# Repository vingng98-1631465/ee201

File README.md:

# EE 201
## This is a practice file for fundamentals.
### Changed this for the sake of the practice.

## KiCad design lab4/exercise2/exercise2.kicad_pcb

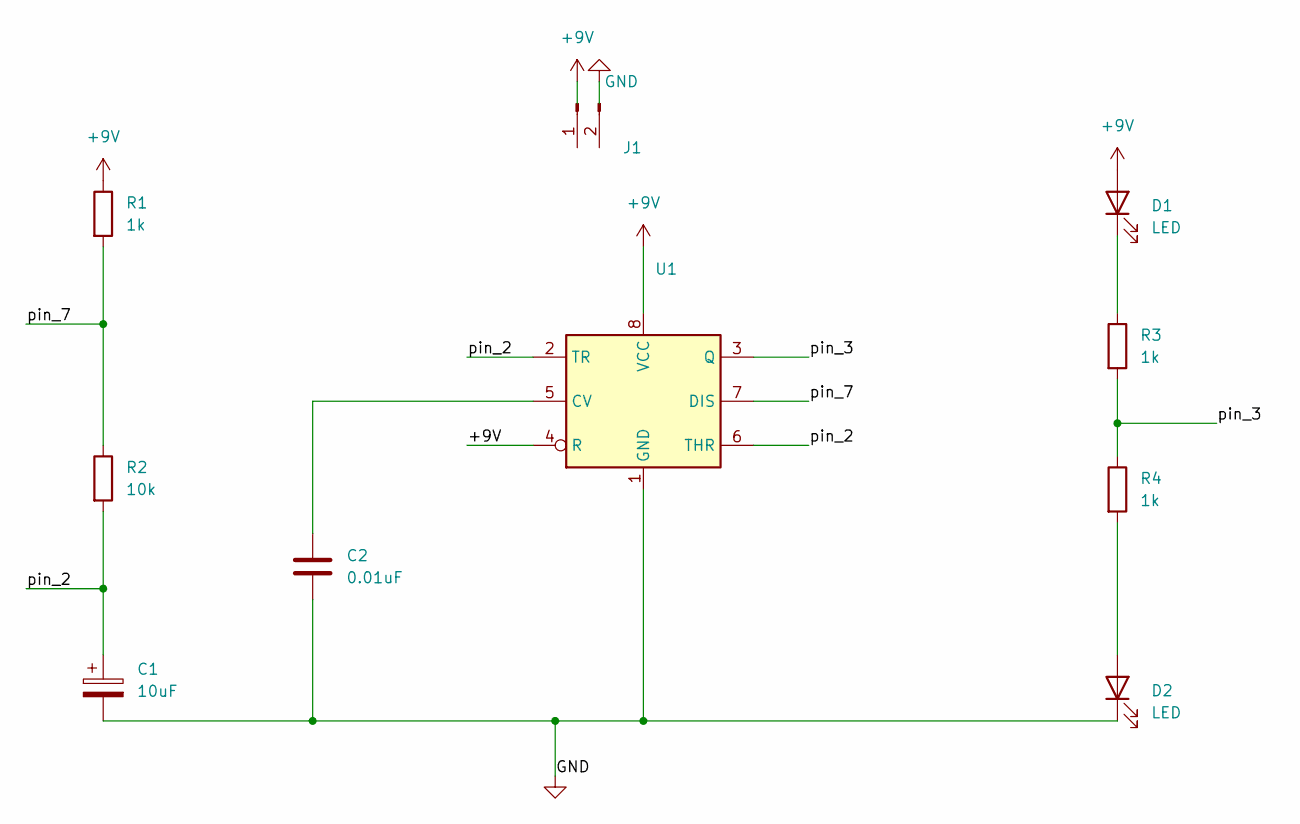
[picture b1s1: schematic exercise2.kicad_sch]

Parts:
C1: 10uF; CP_EIA-3216-18_Kemet-A_Pad1.58x1.35mm_HandSolder
C2: 0.01uF; C_0805_2012Metric_Pad1.18x1.45mm_HandSolder
D1, D2: LED; LED_1206_3216Metric_Pad1.42x1.75mm_HandSolder
J1: J1; TerminalBlock_bornier-2_P5.08mm
R1, R3, R4: 1k; R_0805_2012Metric_Pad1.20x1.40mm_HandSolder
R2: 10k; R_0805_2012Metric_Pad1.20x1.40mm_HandSolder
U1: U1; SOIC-8-1EP_3.9x4.9mm_P1.27mm_EP2.29x3mm

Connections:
+9V: D1.2 (A), R1.1, U1.4 (R), U1.8 (VCC)
/pin_2: C1.1, R2.2, U1.2 (TR), U1.6 (THR)
/pin_3: R3.2, R4.1, U1.3 (Q)
/pin_7: R1.2, R2.1, U1.7 (DIS)
GND: C1.2, C2.2, D2.1 (K), U1.1 (GND)
unnamed: C2.1, U1.5 (CV)
unnamed: D1.1 (K), R3.1
unnamed: D2.2 (A), R4.2

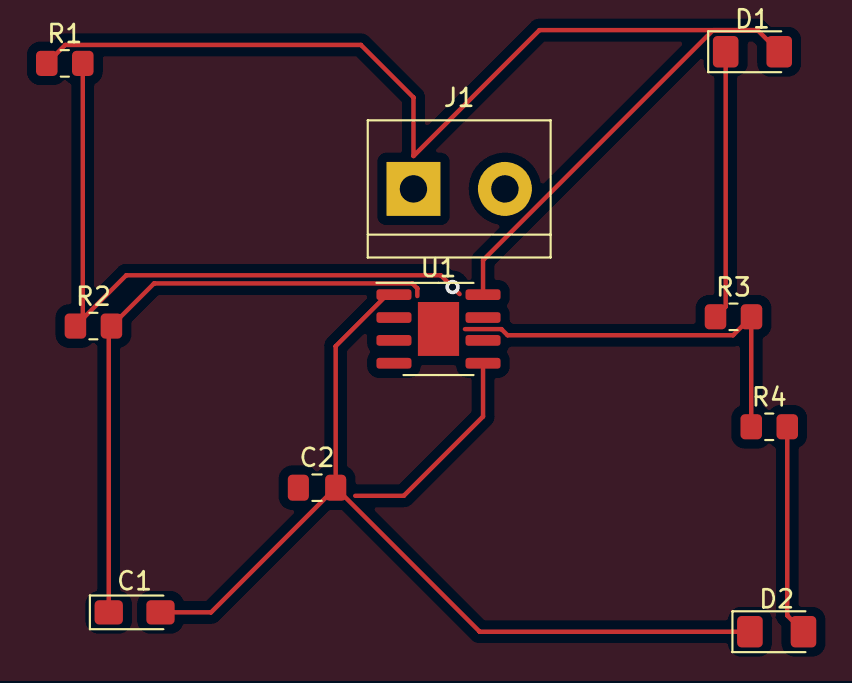
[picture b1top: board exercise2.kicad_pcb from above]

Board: 2 copper layers, 10 parts (0 on the bottom side), 8 nets.

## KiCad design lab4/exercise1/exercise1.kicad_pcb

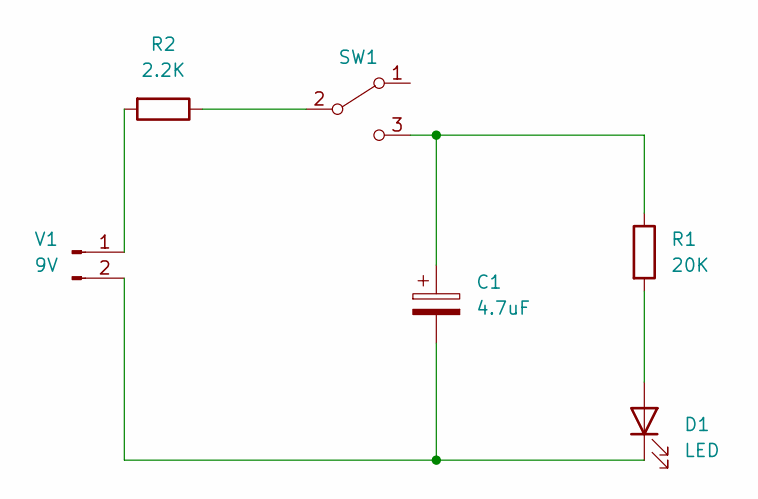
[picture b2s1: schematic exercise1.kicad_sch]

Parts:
C1: 4.7uF; C_Radial_D5.0mm_H5.0mm_P2.00mm
D1: LED; LED_D5.0mm
R1: 20K; R_Axial_DIN0516_L15.5mm_D5.0mm_P20.32mm_Horizontal
R2: 2.2K; R_Axial_DIN0516_L15.5mm_D5.0mm_P20.32mm_Horizontal
SW1: SW_SPDT; SW_E-Switch_EG1224_SPDT_Angled
V1: 9V; JST_PH_B2B-PH-K_1x02_P2.00mm_Vertical

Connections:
unnamed: C1.1, R1.1, SW1.3 (C)
unnamed: C1.2, D1.1 (K), V1.2
unnamed: D1.2 (A), R1.2
unnamed: R2.1, SW1.2 (B)
unnamed: R2.2, V1.1

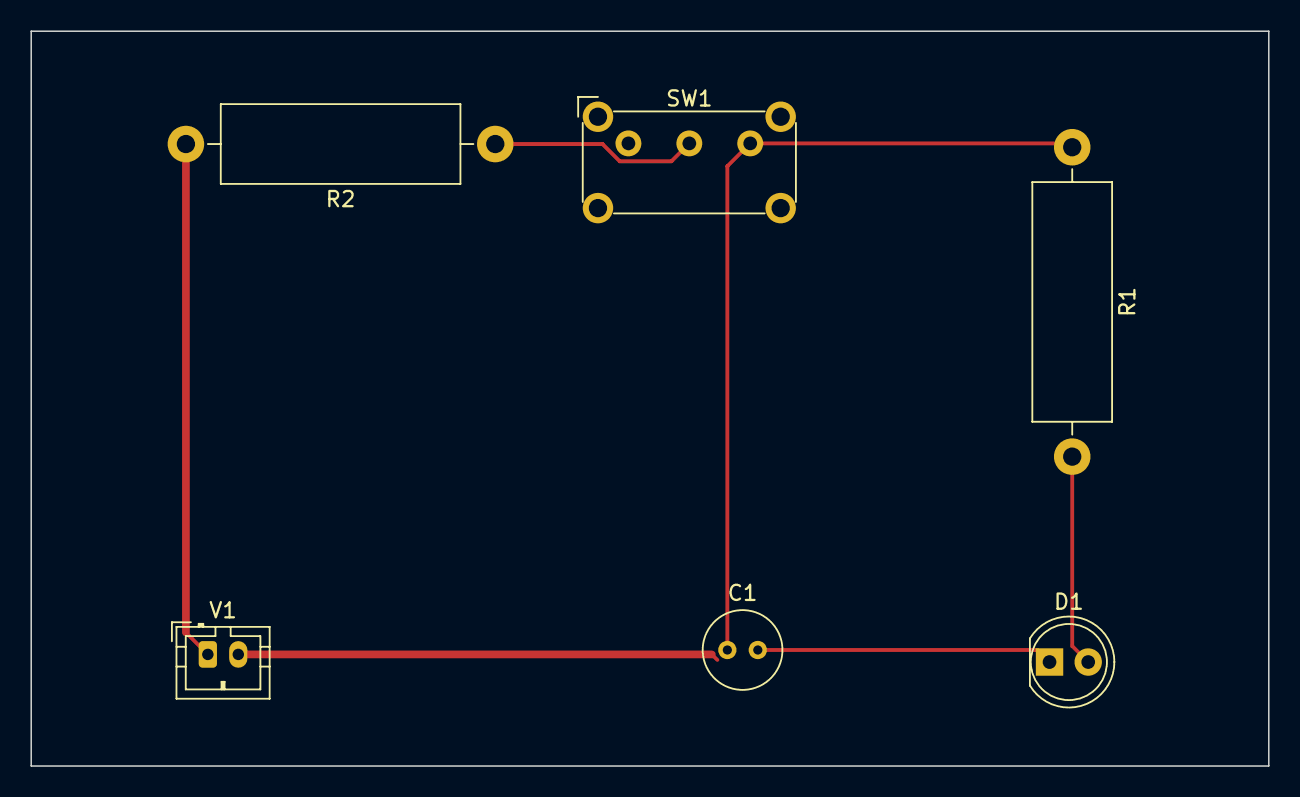
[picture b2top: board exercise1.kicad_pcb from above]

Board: 2 copper layers, 81.3 x 48.3 mm, 6 parts (0 on the bottom side), 5 nets.

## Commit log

2023-01-13 edited readme for practice exercise
2023-01-13 second commit
2023-01-13 Removed extra folder
2023-01-20 uploading lab2
2023-01-27 adding lab 4
2023-02-03 adding lab5
2023-02-10 adding lab 4 changes with pcb
2023-02-17 adding gerber and drill files
2023-03-10 adding lab 8
